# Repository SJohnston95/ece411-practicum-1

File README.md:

# ECE411 Practicum 
The main goal of this project is to gain project management experience, and pass ECE411.

### Resources
- [Github Markdown Cheatsheet](https://github.com/adam-p/markdown-here/wiki/Markdown-Cheatsheet)
- [Atmel 8-bit AVR controller](http://ww1.microchip.com/downloads/en/DeviceDoc/Atmel-8271-8-bit-AVR-Microcontroller-ATmega48A-48PA-88A-88PA-168A-168PA-328-328P_datasheet_Complete.pdf)

### Live Notes
- [Meeting Notes](https://docs.google.com/document/d/19kvDTP8waEN3RQ6yVrNDx6z7Xe4eh67vW1i40oPSDoY/edit?usp=sharing)
- [Bill of Materials](https://docs.google.com/spreadsheets/d/1W5p3Xew4WHdP0dK88rSV139m2ax4RcH9-pE1J-V8YP8/edit?usp=sharing)

### AVR Pin programming
How to connect the ATmega to the AVR Dragon can be found on page 62 of the [pdf for Atmel
AVR
Dragon](https://github.com/philiparola/ece411-practicum/blob/master/datasheets/atmel-42723-avr-dragon_userguide.pdf)

[Code to program the ATmega](http://www.avr-tutorials.com/digital/about-avr-8-bit-microcontrollers-digital-io-ports)

### Programming ATMEGA328 onboard with AVR Dragon
Using the Arduino IDE go to 'sketch/export compiled binary'.
This will compile your code and output it to a pair of *.hex files in the code directory.

We will be using the *.hex files that does not include a bootloader.

In Ateml Studio, go to 'Tools/Device Programming'. Select 'AVR Dragon' as the tool, 'ATmega328P' as the device, and 'ISP' as the interface, click apply, then when it accept that, click 'read' under device signature.

If it reads a device signature the device is correctly plugged in, now go to the 'Fuses' menu on the left. Uncheck the checkbox corresponding to 'LOW.CKDIV8'. This disables the clock divider that lowers the internal clock speed.

If you would like to enable output of the internal clock to pin 14 for power testing, check 'LOW.CKOUT'.

When done setting fuses, click 'program' so set the fuses on the chip.

Now go to the 'Memories' menu. Under 'Flash' use the file browser to navigate to the *.hex file you compiled earlier, and click 'Program' to program the chip.

#ADC contact
http://maxembedded.com/2011/06/the-adc-of-the-avr/

#SPI connections
http://maxembedded.com/2013/11/the-spi-of-the-avr/#Master_Slave

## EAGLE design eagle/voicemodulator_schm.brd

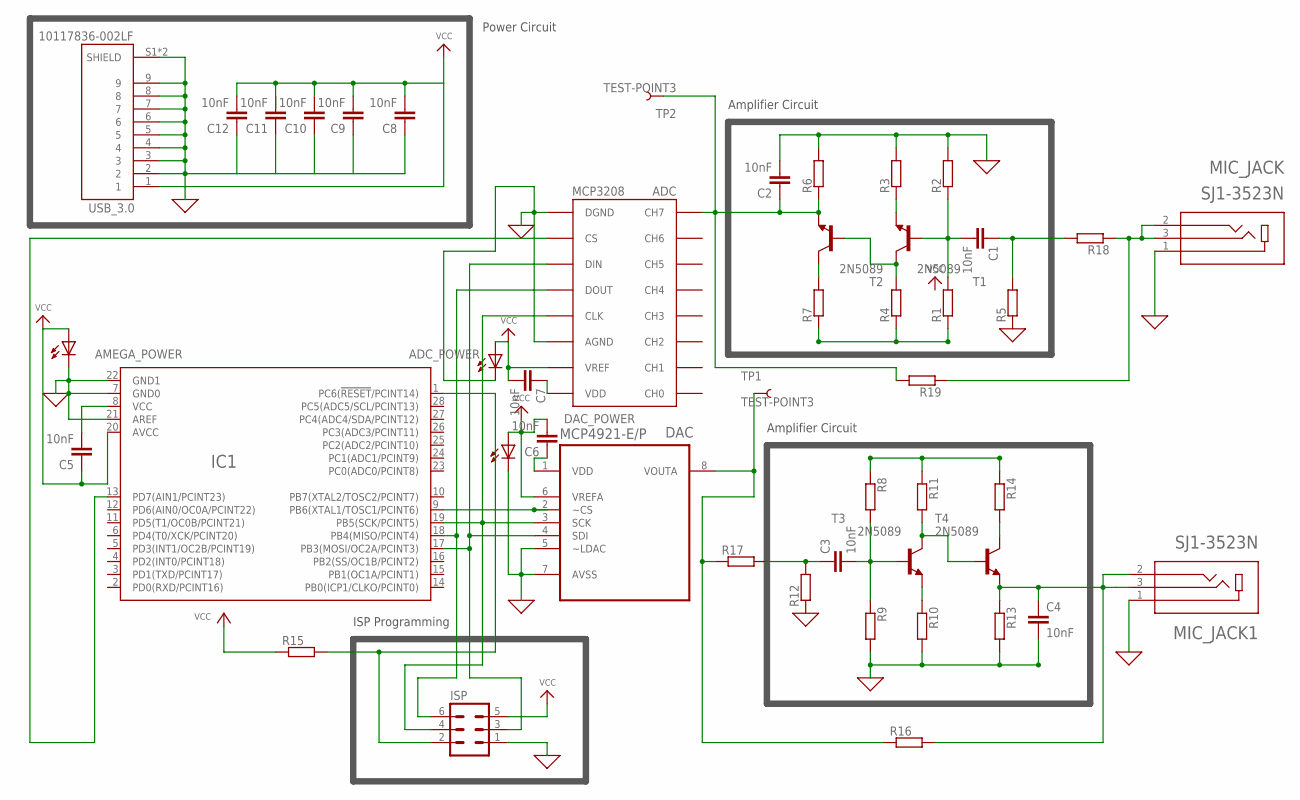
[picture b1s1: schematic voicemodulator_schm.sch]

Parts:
ADC: MCP3208; DIL16
ADC_POWER: LED10MM
AMEGA_POWER: LED10MM
C1, C2, C3, C4, C5, C6, C7, C8, C9, C10, C11, C12: 10nF; 0603
DAC: MCP4921-E/P; DIP254P762X432-8
DAC_POWER: LED10MM
IC1: ATMEGA48/88/168/328-PU(DIP28)PU; DIL28
ISP: MA03-2
MIC_JACK, MIC_JACK1: SJ1-3523N; CUI_SJ1-3523N
R1, R2, R3, R4, R5, R6, R7, R8, R9, R10, R11, R12, R13, R14, R15, R16, R17, R18, R19: SMR-WAV; SMS-WAV
T1, T2, T3, T4: 2N5089; TO92
TP1, TP2: TEST-POINT3; PAD.03X.03
USB_3.0: 10117836-002LF; AMPHENOL_10117836-002LF

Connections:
GND: ADC.AGND, ADC.DGND, ADC_POWER.K (C), AMEGA_POWER.K (C), C2.2, C4.2, C8.1, C9.1, C10.1, C11.1, C12.1, DAC.5 (~LDAC), DAC.7 (AVSS), DAC_POWER.K (C), IC1.7 (GND0), IC1.21 (AREF), IC1.22 (GND1), ISP.1, MIC_JACK.1, MIC_JACK1.1, R2.1, R3.1, R5.2, R6.1, R9.1, R10.1, R12.2, R13.1, USB_3.0.2, USB_3.0.3, USB_3.0.4, USB_3.0.5, USB_3.0.6, USB_3.0.7, USB_3.0.8, USB_3.0.9, USB_3.0.S1 (SHIELD), USB_3.0.S2 (SHIELD)
unnamed: C1.1, R5.1, R18.1
unnamed: ADC.DOUT, IC1.18 (PB4(MISO/PCINT4)), ISP.6
unnamed: C1.2, R1.1, R2.2, T1.2 (B)
unnamed: DAC.8 (VOUTA), R16.2, R17.2, TP1.P$1
unnamed: ADC.CH7, C2.1, R6.2, R19.1, T2.3 (E), TP2.P$1
unnamed: R7.1, T2.1 (C)
unnamed: R3.2, T1.3 (E)
unnamed: R4.1, T1.1 (C), T2.2 (B)
unnamed: C3.2, R8.1, R9.2, T3.2 (B)
unnamed: R1.2, R4.2, R7.2
unnamed: C4.1, MIC_JACK1.2, MIC_JACK1.3, R13.2, R16.1, T4.3 (E)
unnamed: R14.1, T4.1 (C)
unnamed: R10.2, T3.3 (E)
unnamed: R11.1, T3.1 (C), T4.2 (B)
unnamed: R8.2, R11.2, R14.2
unnamed: ADC.DIN, DAC.4 (SDI), IC1.17 (PB3(MOSI/OC2A/PCINT3)), ISP.3
unnamed: ADC.CLK, DAC.3 (SCK), IC1.19 (PB5(SCK/PCINT5)), ISP.4
unnamed: C6.1, DAC.1 (VDD)
unnamed: ADC.CS, IC1.13 (PD7(AIN1/PCINT23))
unnamed: DAC.2 (~CS), IC1.9 (PB6(XTAL1/TOSC1/PCINT6))
unnamed: ADC.VDD, C7.1
unnamed: IC1.1 (PC6(!RESET!/PCINT14)), ISP.2, R15.1
unnamed: C3.1, R12.1, R17.1
unnamed: MIC_JACK.2, MIC_JACK.3, R18.2, R19.2
unnamed: C5.2, IC1.8 (VCC)
VCC: ADC.VREF, ADC_POWER.A, AMEGA_POWER.A, C5.1, C6.2, C7.2, C8.2, C9.2, C10.2, C12.2, DAC.6 (VREFA), DAC_POWER.A, IC1.20 (AVCC), ISP.5, R15.2, USB_3.0.1

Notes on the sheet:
Amplifier Circuit
ISP Programming
Power Circuit

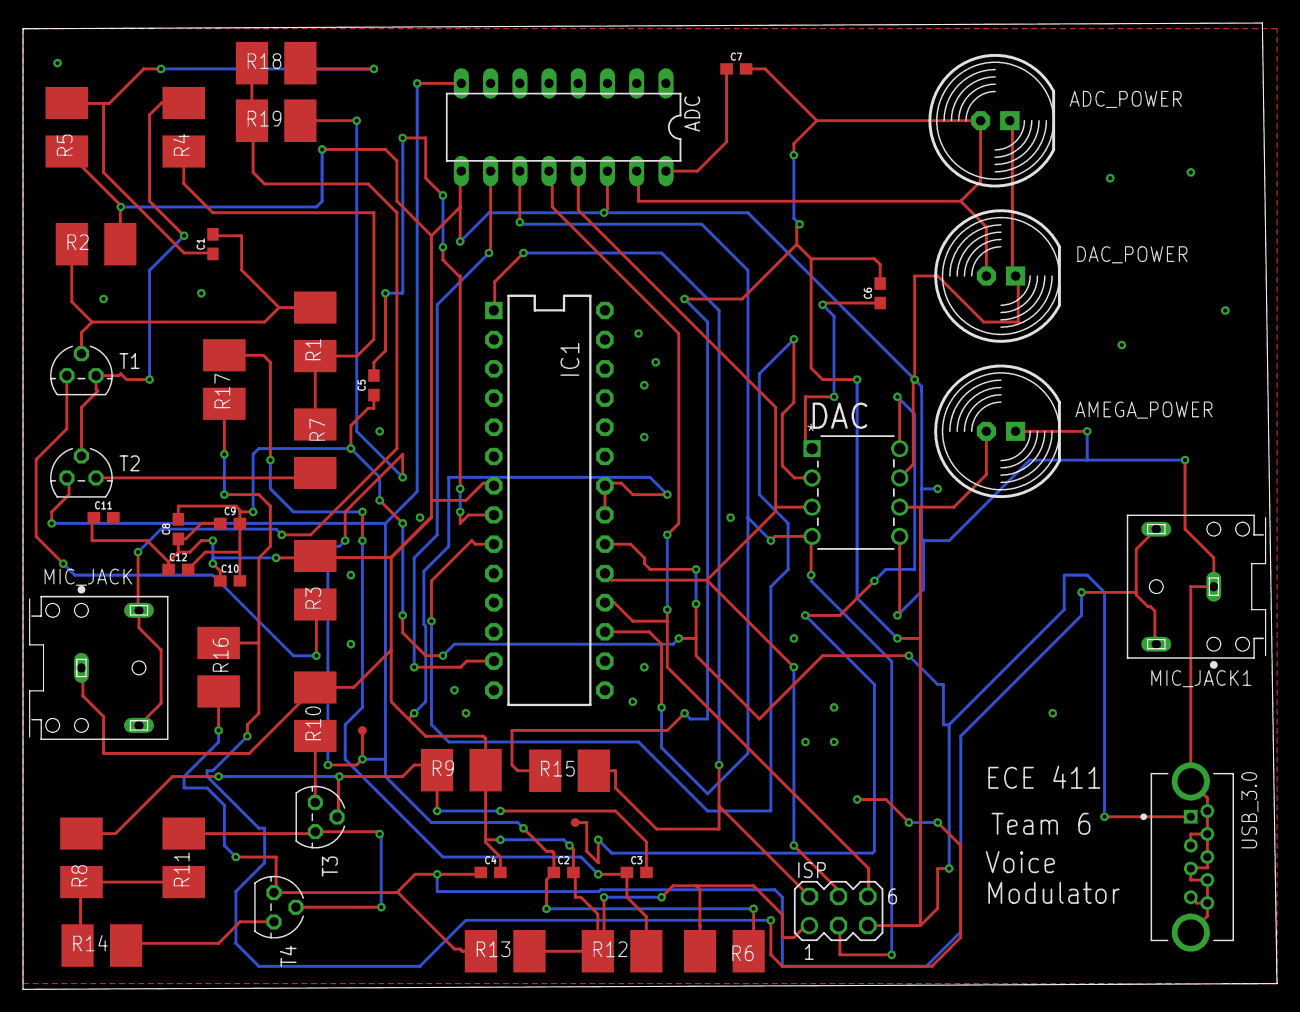
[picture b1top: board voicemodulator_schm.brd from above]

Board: 2 copper layers, 109.0 x 84.0 mm, 47 parts (0 on the bottom side), 27 nets.

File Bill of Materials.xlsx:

Qty | Value | Device | Package | Parts | Description | MANUFACTURER | MPN
1.0 |  | ATMEGA48/88/168/328-PU(DIP28)PU | DIL28 | ATMEGA48A
1.0 |  | MA03-2 | MA03-2 | ISP | PIN HEADER
14.0 |  | SMR-WAV | SMS-WAV | R1, R2, R3, R4, R5, R6, R7, R8, R9, R10, R11, R12, R13, R14 | SMD SHUNT RESISTOR
4.0 | 10nF | 10NF-0603-50V-10% | 603 | C1, C2, C3, C4 | 0.01uF/10nF/10,000pF ceramic capacitors
4.0 | 2N5089 | 2N5089 | TO92 | T1, T2, T3, T4 | NPN TRANSISTOR
1.0 | MCP3208 | MCP3208 | DIL16 | ADC
1.0 | MCP4921-E/MS | MCP4921-E/MS | MSOP-8 | DAC | Digital-to-Analog Converter
1.0 | SJ1-3523N | SJ1-3523N | CUI_SJ1-3523N | MIC_JACK | 3.5 mm Right-Angle Stereo Jack, 3 Pin PCB Mount, Non-Threaded | CUI
3.0 |  | Microphones |  | HUACAM YYPJ-01-1

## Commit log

2018-10-07 Meeting Notes For 10/7 Meeting
    Decided project, bought some parts.
2018-10-08 Add README with some useful links
2018-10-09 Make minor README edit to prove write access.
2018-10-14 I added the AVR pin programming document
2018-10-14 Bill of Materials
    Initial Upload- updated w/ price per, quantity and resource links.
2018-10-14 This is the main.c program that we're using
    This should flash the lights on and off.
2018-10-18 Working main file for the led to flash on and off.
2018-10-19 Add datasheets for ATmega processors and AVR Dragon
2018-10-19 Edit README
2018-10-21 Main2.0
    Here's the main we are using to communicate with the DAC. We're getting the data from the ADC, storing it and trying to move it to the DAC. This is not working code yet, and we are still learning. "P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
2018-10-21 Main2.1
    Here's a copy of Main2.0 separated into functions. This is a more sane approach towards the input/output dichotomy.
2018-10-21 Rename main - Copy.cpp to main2.1
2018-10-22 Main 2.2
    Here's a copy of the most up to date Main file. I found a different way to use SPI by using distinct predefined registers. I still cannot get it to work however. I'm not sure why. The 'Data2 = 101010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
2018-10-25 Add datasheet for project hardware
2018-10-25 Add preliminary schematic
2018-10-25 Add ISP pin to schematic
2018-10-25 Added component datasheets
2018-10-25 Main 3.0
    Here's a copy of my main file with SPI working correctly. I haven't been able to get this SPI to interface with the dac correctly just yet.
2018-10-28 Project Description Specification
2018-10-28 Added useful EagleCAD files
2018-10-28 Updated with 10/14 Notes
2018-10-28 Reorganized source
2018-10-28 Notes as of 10/28
2018-10-28 Created project
    GCC C++ Executable Project
    Target: ATmega48A
2018-10-28 BOM run from schematic
    May need additional details added such as resources and prices.
2018-10-28 BOM from Schematic
    May want to add additional details such as price, price per, resources and such.
2018-10-28 Libraries used for EAGLE Schematic Design
2018-10-28 Added library code into submodule
2018-10-28 Libraries used from schematic design
2018-10-28 Imported an Arduino library
    As a test
2018-10-28 Tested Arduino sketch import capability
2018-10-28 Added 'library' code to project
2018-10-29 Main 4.0
    I have the DAC working in this version.
2018-10-29 Update schematic and rename folder
    Folder has been renamed to "eagle" so that it's easier to find.
    Schematic and PNG has been updated to a version that has no ERC errors.
    Resistors and capacitor values still need to be assigned.
2018-10-29 Add library with fixed pars for project
    Added a fixed version of ATmega48 DIP package. Also includes ADC, DAC,
    and the specific Mic jack we'll be using.
2018-11-02 Layout from 10/31
2018-11-02 Board Layout from 10/31
2018-11-04 input and output circuits
    Here's my simulations of the input/output circuits I designed
2018-11-04 Delete amplifier_circuit_output.asc
    adding a newer version
2018-11-04 Amplifier_circuit_output
2018-11-04 Pullup resistor added, testpoints at ADC in and DAC out added.
    Pictures, board layout and schematic all updated.
2018-11-04 Found SPI ADC example
    http://extremeelectronics.co.in/avr-tutorials/interfacing-12-bit-spi-adc-mcp3204-with-avr-micro/
2018-11-08 Add Arduino sketch that reads in audio signal
2018-11-08 Added design review notes
2018-11-11 Redundant files committed when unsure of how to use Github
2018-11-11 Renamed eaglecad-things.zip to EagleCad_Workshop.zip
2018-11-11 Redundant
2018-11-11 Added 10 mm Power LEDs
2018-11-11 Added output mic jack.
2018-11-12 Fix incorrect dimensions in eagle library for DIP
    48A DIP device dimensions on layout were incorrect and needed modifying
    to match what is specified in the datasheet.
2018-11-12 Updated for 11/4 and 11/11
2018-11-12 Added picture I forgot to include with 11/11 portion
2018-11-12 Segmented output into two paths with 0 ohm resistors
2018-11-12 Updated with new model that is adjusted to correct Atmega48A dimensions.
2018-11-12 Segmented input with 0 ohm resistors for w/ amp vs. not
2018-11-13 USB 3.0 Type A SMT Library
2018-11-13 USB 3.0 Type A Port Added, pinout TBD
2018-11-14 Made USB 3.0 connections
2018-11-14 BOM updated since USB 3 added
2018-11-14 Add new attempt to read and output ADC0
    Includes more detailed commenting of previous code that implements SPI
    with DAC
2018-11-15 Added name of LEDs and labeling for group/project on silk screen layer
2018-11-15 Attempt 2 with silkscreen layer additions
2018-11-15 Attempt 2 to commit silkscreen changes
2018-11-15 Grounded LEDs on power pins, added bypass caps at power pins
2018-11-15 Fixed erc error I missed on DAC
2018-11-15 Updated trace width to 0.254
2018-11-15 Add caps for input voltage coming in through USB 3.0, remaining wire widths resolved.
2018-11-15 Ground plane and multiple vias added for flooded ground
2018-11-15 Main 4.1
    Here's my code for 4.1, there's very little changes from 4.0 to 4.1. Just some code cleanup on the ADC program, it still doesn't work.
2018-11-16 Delete voicemodulator.png
    Caused conflicts on Windows because voicemodulator.PNG exists
2018-11-19 Main 6.0
    This is main 6.0. It has a working ADC and working DAC. The only thing that is required is voltage amplification on the input and current amplification on the output.
2018-11-25 added mcp3208 arduino code
2018-11-25 Added possible DAC library
2018-11-28 DAC library that we've tested
    Minor edits that caused problems in the original header. Original
    forgot to include SPI. Link to original library is below.
    https://github.com/michd/Arduino-MCP492X
2018-11-28 Successful test code that works with Arduino Nano
    Uses new DAC library. Tested and works.
2018-11-28 Made cleaned up version of main6.cpp in src/passthroughTest
    Made a new project folder with a cleaned up version of main6.cpp, which I believe is the most recent version of the non-arduino code we had working.
    Also contains a project status text file.
    Code should be functionally identical, just easier to read and work with, still needs a lot of work.
2018-11-28 Test plans done
2018-11-29 Added Gantt Chart, closes #17
2018-11-29 Closes #19, added decision matrix and block diagrams
2018-12-01 Started ADC DAC integration test
    Copied working DAC code to new folder to start integrating the ADC in, included new ADC library.
2018-12-02 Creating directory to clean up repository
2018-12-02 Moved from top directory
2018-12-02 Redundant no located in Trobleshooting
2018-12-02 Redundant now located in Troubleshooting
2018-12-02 Cleanup and new arduino_passthrough_test folder.
    Did some cleanup of old files and started a new project folder, ADC library I was testing didn't work out.
2018-12-02 Cleanup docs
2018-12-03 Got acd_dac "working".
    Not totally working, but we now have a passthrough of a sort.
2018-12-03 Passthrough working
    fixes #13
2018-12-05 Updated Gantt Chart to be current by presentation
2018-12-05 Updated Gantt Chart for presentation
2018-12-05 Updated Readme for uploading to board. Also made everything work(ish).

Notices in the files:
parts and their libraries:
SparkFun-Capacitors: Licensing: Creative Commons ShareAlike 4.0 International - https://creativecommons.org/licenses/by-sa/4.0
